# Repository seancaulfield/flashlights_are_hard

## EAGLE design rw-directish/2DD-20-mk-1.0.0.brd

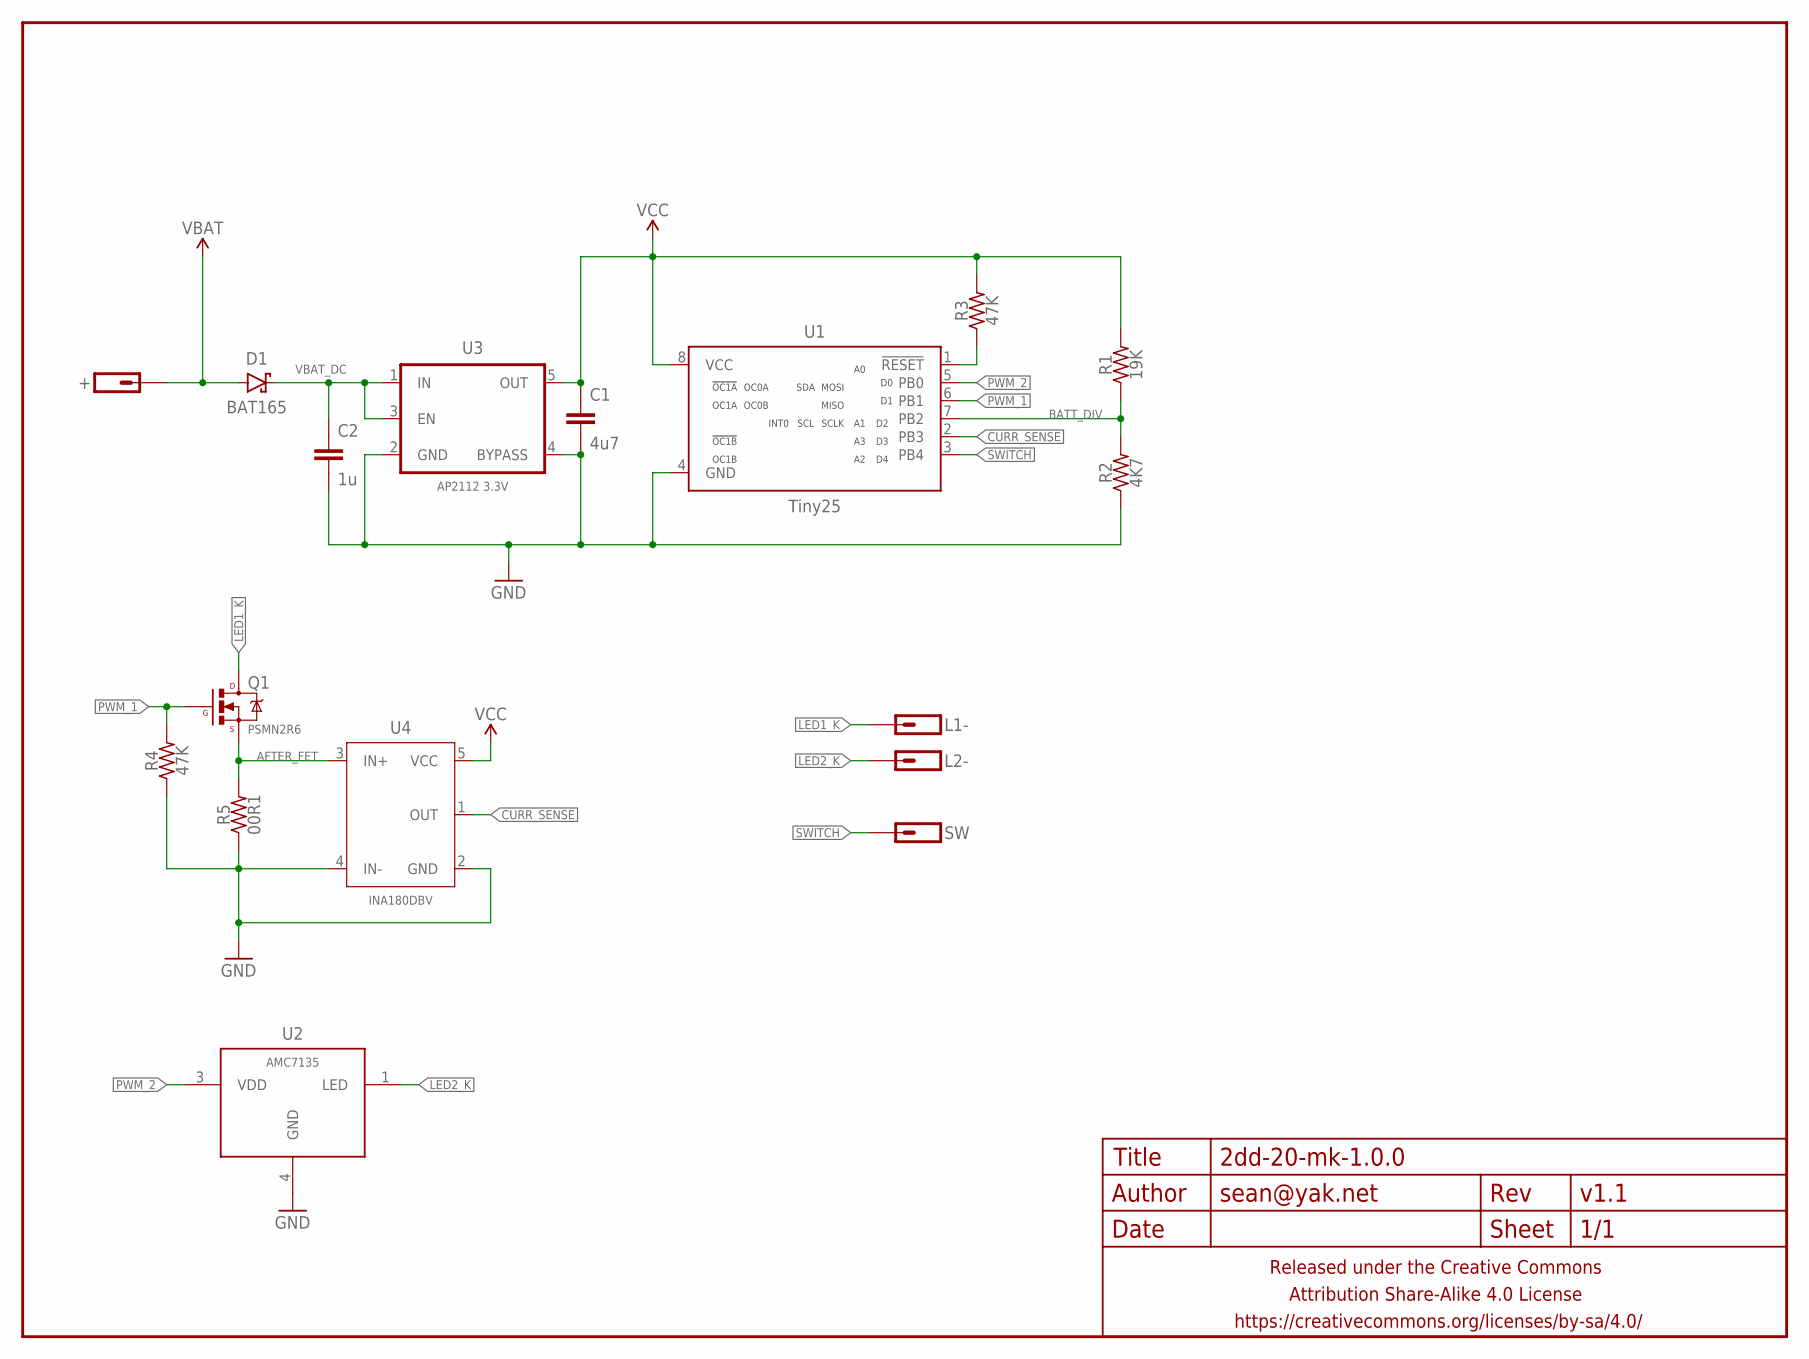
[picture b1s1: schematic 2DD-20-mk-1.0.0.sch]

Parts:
+: M01PTH-1MM-CIR-NS; 1X01-1MM-CIR-NS
C1: 4u7; C0603-TIGHTER
C2: 1u; C0402
D1: BAT165; SOD323-SCHOTTKY
FRAME1: FRAME-LETTERNO_PACKAGE; DUMMY
L1-: M011X01-0.9MM-CIR; 1X01-0.9MM-CIR
L2-: M01PTH-0.8MM-CIR; 1X01-0.8MM-CIR
Q1: PSMN2R6; POWERPACK-SO-8
R1: 19K; R0402
R2: 4K7; R0402
R3, R4: 47K; R0402
R5: 00R1; R1206
SW: M01SMD-0.8MM-DIA-NS; 1X01-SMD-0.8MM-DIA-NS
U1: Tiny25; SO08-NARROWER
U2: AMC7135; SOT89-NOTHERM-ROUNDED-LESS
U3: AP2112 3.3V; SOT23-5
U4: INA180DBV; SOT23-5

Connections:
AFTER_FET: Q1.1 (S), Q1.2 (S), Q1.3 (S), R5.2, U4.3 (IN+)
BATT_DIV: R1.1, R2.2, U1.7 (PB2)
CURR_SENSE: U1.2 (PB3), U4.1 (OUT)
GND: C1.2, C2.2, R2.1, R4.1, R5.1, U1.4 (GND), U2.4 (GND), U3.2 (GND), U3.4 (BYPASS), U4.2 (GND), U4.4 (IN-)
LED1_K: L1-.P$1, Q1.5678 (D)
LED2_K: L2-.1, U2.1 (LED)
unnamed: R3.1, U1.1 (!RESET)
PWM_1: Q1.4 (G), R4.2, U1.6 (PB1)
PWM_2: U1.5 (PB0), U2.3 (VDD)
SWITCH: SW.P$1, U1.3 (PB4)
VBAT: +.1, D1.A
VBAT_DC: C2.1, D1.C, U3.1 (IN), U3.3 (EN)
VCC: C1.1, R1.2, R3.2, U1.8 (VCC), U3.5 (OUT), U4.5 (VCC)

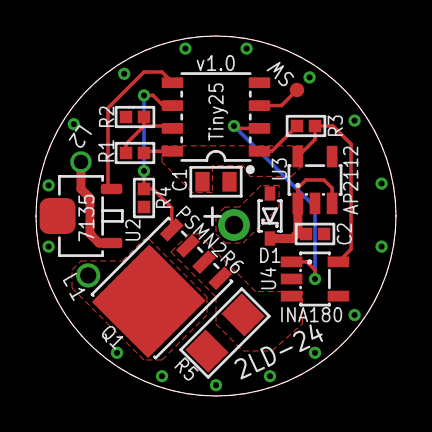
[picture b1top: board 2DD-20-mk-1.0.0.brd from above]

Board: 2 copper layers, 20.0 x 20.0 mm, 18 parts (0 on the bottom side), 13 nets.

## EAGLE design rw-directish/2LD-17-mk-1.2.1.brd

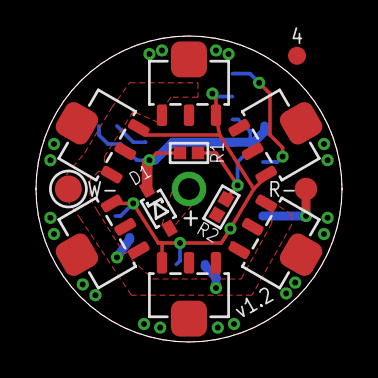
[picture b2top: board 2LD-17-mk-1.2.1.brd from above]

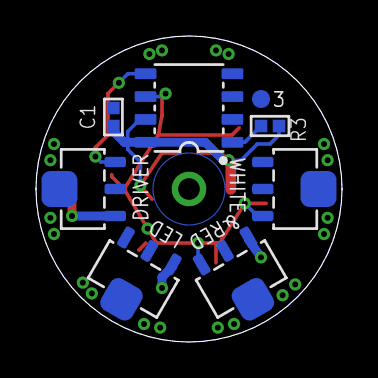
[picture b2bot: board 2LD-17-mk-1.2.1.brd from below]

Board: 2 copper layers, 17.0 x 17.0 mm, 22 parts (8 on the bottom side), 11 nets.

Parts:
3, 4: M01SMD-1MM-DIA-NS; 1X01-SMD-1MM-DIA-NS
+: M01PTH-1.2MM-NS; 1X01-1.2MM-NS
C1: 1u; C0402
D1: BAT165; SOD323-SCHOTTKY
FRAME1: FRAME-LETTERNO_PACKAGE; DUMMY
R1: 19K; R0402
R2: 4K7; R0402
R3: 10K; R0402
R-: M01SMD-1.25MM-DIA; 1X01-SMD-1.25MM-DIA-NS
U0: Tiny13; SO08-NARROWER
U1, U2, U3, U4, U5, U6, U7, U8, U9, U10: AMC7135; SOT89-NOTHERM-ROUNDED
W-: M01SMD-1.5MM-DIA-NS; 1X01-SMD-1.5MM-DIA-NS

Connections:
3: 3.P$1, U0.2
4: 4.P$1, U0.3
BATT_DIV: R1.1, R2.2, U0.7
GND: C1.2, R2.1, U0.4, U1.4@1, U1.4@2, U2.4@1, U2.4@2, U3.4@1, U3.4@2, U4.4@1, U4.4@2, U5.4@1, U5.4@2, U6.4@1, U6.4@2, U7.4@1, U7.4@2, U8.4@1, U8.4@2, U9.4@1, U9.4@2, U10.4@1, U10.4@2
unnamed: R3.1, U0.1
PWM_R: U0.5, U10.3
PWM_W: U0.6, U1.3, U2.3, U3.3, U4.3, U5.3, U6.3, U7.3, U8.3, U9.3
RED_K: R-.P$1, U10.1
VBAT: +.P$1, D1.A
VCC: C1.1, D1.C, R1.2, R3.2, U0.8
WHITE_K: U1.1, U2.1, U3.1, U4.1, U5.1, U6.1, U7.1, U8.1, U9.1, W-.P$1

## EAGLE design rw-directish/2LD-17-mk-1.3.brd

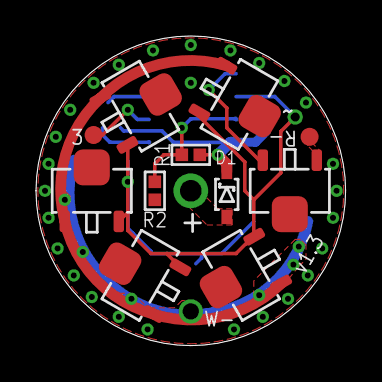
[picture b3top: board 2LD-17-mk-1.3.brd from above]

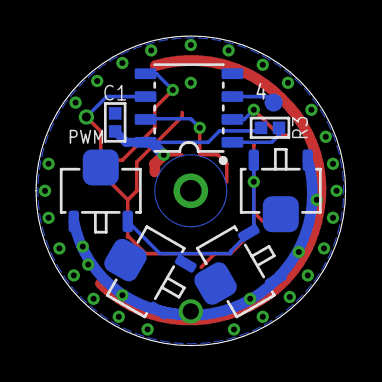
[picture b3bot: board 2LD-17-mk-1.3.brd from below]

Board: 2 copper layers, 17.2 x 17.2 mm, 22 parts (8 on the bottom side), 11 nets.

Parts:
3, 4: M01SMD-1MM-DIA-NS; 1X01-SMD-1MM-DIA-NS
+: M01PTH-1.2MM-NS; 1X01-1.2MM-NS
C1: 1u; C0402
D1: BAT165; SOD323-SCHOTTKY
FRAME1: FRAME-LETTERNO_PACKAGE; DUMMY
R1: 19K; R0402
R2: 4K7; R0402
R3: 10K; R0402
R-: M01SMD-1MM-DIA-NS; 1X01-SMD-1MM-DIA-NS
U1: Tiny25; SO08-NARROWER
U2, U3, U4, U5, U6, U7, U8, U9, U10, U11: AMC7135; SOT89-NOTHERM-ROUNDED-LESS
W-: M011X01-0.9MM-CIR; 1X01-0.9MM-CIR

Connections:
3: 3.P$1, U1.2
4: 4.P$1, U1.3
BATT_DIV: R1.1, R2.2, U1.7
GND: C1.2, R2.1, U1.4, U2.4, U3.4, U4.4, U5.4, U6.4, U7.4, U8.4, U9.4, U10.4, U11.4
unnamed: R3.1, U1.1
PWM_R: U1.5, U2.3
PWM_W: U1.6, U3.3, U4.3, U5.3, U6.3, U7.3, U8.3, U9.3, U10.3, U11.3
RED_K: R-.P$1, U2.1
VBAT: +.P$1, D1.A
VCC: C1.1, D1.C, R1.2, R3.2, U1.8
WHITE_K: U3.1, U4.1, U5.1, U6.1, U7.1, U8.1, U9.1, U10.1, U11.1, W-.P$1

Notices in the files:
parts and their libraries:
a_parts: Released under the Creative Commons Attribution Share-Alike 4.0 License
a_parts: https://creativecommons.org/licenses/by-sa/4.0
a_parts: Released under the Creative Commons
